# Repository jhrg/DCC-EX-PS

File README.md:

# DCC-EX-PS

## Generate a QR code

Goto https://www.the-qrcode-generator.com/ and get the 1000px QR code PNG.

Open in the KiCAD Image Converter

Set the size to be 20 x 20 mm (e.g.) and export to a files.

The QR code will be in a kicad_mod file. Copy this to the local
footprint.petty dir and import to the footprints. 

Drop the footprint onto the back layer. If needed, Edit it and set the
layer as 'Back.' The footprint/QR-code should show up as reversed. 

Check the 3D view. Check the QR code using a phone. etc.

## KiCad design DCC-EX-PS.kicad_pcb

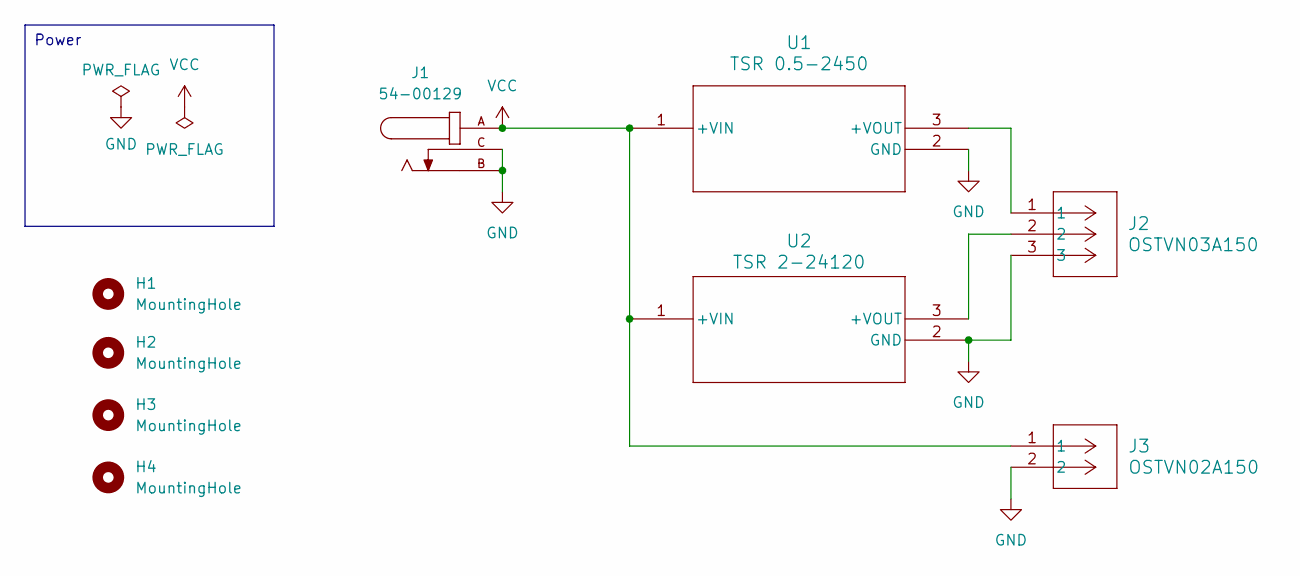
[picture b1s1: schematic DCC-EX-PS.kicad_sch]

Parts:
H1, H2, H3, H4: MountingHole; MountingHole_3mm
J1: 54-00129; TENSILITY_54-00129; PARTREV A
J2: OSTVN03A150; CONN3_OSTVN03A150_OST
J3: OSTVN02A150; CONN_OSTVN02A150_OST
U1: TSR 0.5-2450; TSR0P5_TRP
U2: TSR 2-24120; TSR2-SINGLE_TRP

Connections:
GND: J1.B, J1.C, J2.3, J3.2, U1.2 (GND), U2.2 (GND)
unnamed: J2.1, U1.3 (+VOUT)
unnamed: J2.2, U2.3 (+VOUT)
VCC: J1.A, J3.1, U1.1 (+VIN), U2.1 (+VIN)

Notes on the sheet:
Power

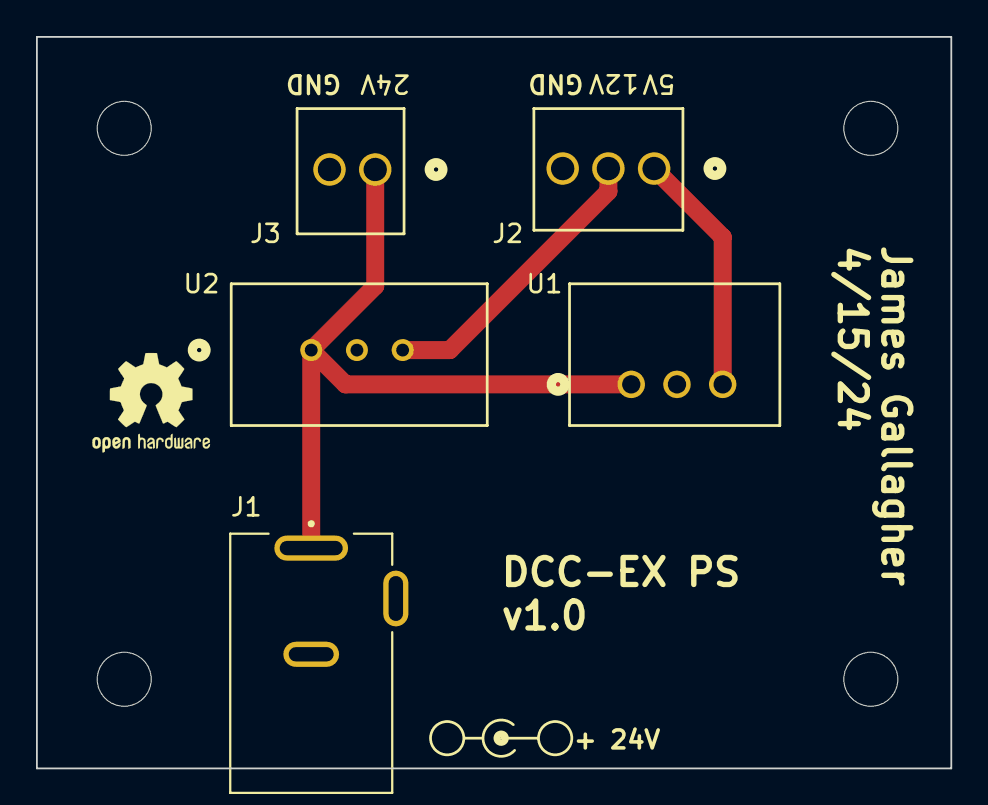
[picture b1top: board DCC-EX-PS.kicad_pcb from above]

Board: 2 copper layers, 50.8 x 40.6 mm, 9 parts (0 on the bottom side), 4 nets.

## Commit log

2024-04-17 Added files
2024-04-17 Added QR code to back of the board
2024-04-18 Added more graphics and 24v out terminal
2024-06-16 KiCAD version 8
